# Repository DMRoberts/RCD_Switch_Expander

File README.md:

# RCD Switch Expander
PCB and Panel files for a Eurorack switch expander. Designed for the 4MS Rotating Clock Divider (RCD), however it should be useable with any Eurorack module where a SPDT switch can replace a three-pin jumper.

### PCB

PCB is designed using KiCad.

### Panel

The panel was produced via Front Panel Express ([https://www.frontpanelexpress.com/](https://www.frontpanelexpress.com/)). The included Front Design file (FPD) can be used to order the same panel. The panel text was created in Affinity Designer, and imported into Front Design as a graphic object. To change the text, you can either:

A. Replace the graphic object with text engravings:

1. Delete the graphic layer in Front Design.
2. Insert Front Design text engravings.

B. Update the graphic object:

1. Open the included .AI file in a program that can edit Adobe Illustrator files.
2. Edit the text.
3. Hide all non-text layers (they are only there as a reference)
4. Export to PDF
5. Replace the PDF in the 'File' field of the graphic object with your updated object.

### Bill of Materials

| Description                                  | Quantity | Manufacturer Part #  | Notes                                                                                                       |
|----------------------------------------------|----------|----------------------|-------------------------------------------------------------------------------------------------------------|
| Sub Miniature SPDT On-On Switches            | 6        | 108-0042-EVX         | Switch with same specs available from Thonk (DW1):   https://www.thonk.co.uk/shop/sub-mini-toggle-switches/ |
| 1 Row x 3 Pin Male Pin Header (2.54   pitch) | 6        | 68001-403HLF         | Optional, can also solder wires directly to board, or break apart a   longer row of 2.54 mm headers         |
| 2.54 mm Female to Female Jumper Cables       | 12       | Various - Check Ebay | Optinal, if used need 12 for RCD (2 for each switch)                                                        |

<br>

<br>

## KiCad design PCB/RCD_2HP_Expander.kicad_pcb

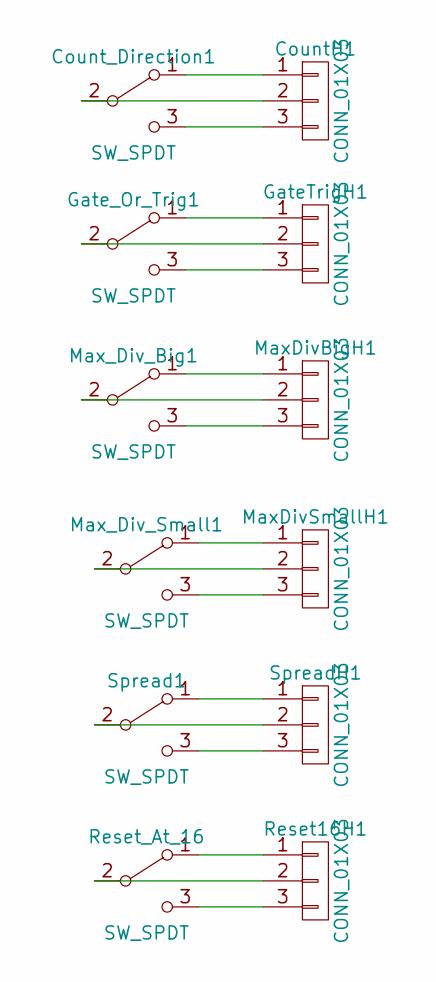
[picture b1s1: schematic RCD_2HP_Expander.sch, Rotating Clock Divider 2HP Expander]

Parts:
CountH1: CONN_01X03; Pin_Header_Straight_1x03_Pitch2.54mm
Count_Direction1: SW_SPDT; DW1-SPDT-ON-ON
GateTrigH1: CONN_01X03; Pin_Header_Straight_1x03_Pitch2.54mm
Gate_Or_Trig1: SW_SPDT; DW1-SPDT-ON-ON
MaxDivBigH1: CONN_01X03; Pin_Header_Straight_1x03_Pitch2.54mm
MaxDivSmallH1: CONN_01X03; Pin_Header_Straight_1x03_Pitch2.54mm
Max_Div_Big1: SW_SPDT; DW1-SPDT-ON-ON
Max_Div_Small1: SW_SPDT; DW1-SPDT-ON-ON
Reset16H1: CONN_01X03; Pin_Header_Straight_1x03_Pitch2.54mm
Reset_At_16: SW_SPDT; DW1-SPDT-ON-ON
Spread1: SW_SPDT; DW1-SPDT-ON-ON
SpreadH1: CONN_01X03; Pin_Header_Straight_1x03_Pitch2.54mm

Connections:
unnamed: CountH1.1, Count_Direction1.1 (A)
unnamed: CountH1.2, Count_Direction1.2 (B)
unnamed: CountH1.3, Count_Direction1.3 (C)
unnamed: GateTrigH1.1, Gate_Or_Trig1.1 (A)
unnamed: GateTrigH1.2, Gate_Or_Trig1.2 (B)
unnamed: GateTrigH1.3, Gate_Or_Trig1.3 (C)
unnamed: MaxDivBigH1.1, Max_Div_Big1.1 (A)
unnamed: MaxDivBigH1.2, Max_Div_Big1.2 (B)
unnamed: MaxDivBigH1.3, Max_Div_Big1.3 (C)
unnamed: MaxDivSmallH1.1, Max_Div_Small1.1 (A)
unnamed: MaxDivSmallH1.2, Max_Div_Small1.2 (B)
unnamed: MaxDivSmallH1.3, Max_Div_Small1.3 (C)
unnamed: Reset16H1.1, Reset_At_16.1 (A)
unnamed: Reset16H1.2, Reset_At_16.2 (B)
unnamed: Reset16H1.3, Reset_At_16.3 (C)
unnamed: Spread1.1 (A), SpreadH1.1
unnamed: Spread1.2 (B), SpreadH1.2
unnamed: Spread1.3 (C), SpreadH1.3

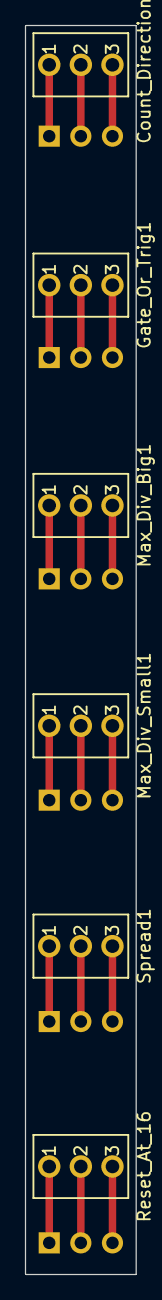
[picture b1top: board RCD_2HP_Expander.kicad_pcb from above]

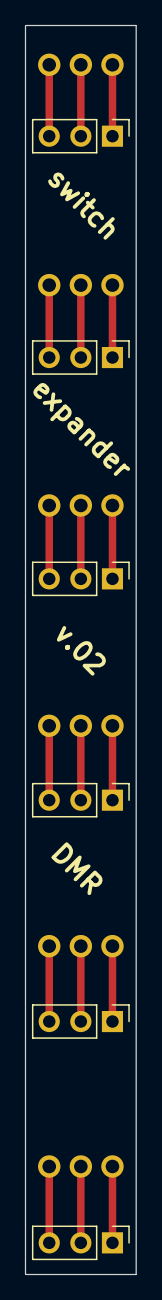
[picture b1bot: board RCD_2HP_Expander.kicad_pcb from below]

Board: 2 copper layers, 8.9 x 100.3 mm, 12 parts (6 on the bottom side), 18 nets.

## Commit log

2021-10-18 Update README, add files
